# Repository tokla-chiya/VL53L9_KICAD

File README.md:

# VL53L9CX I2C-only breakout

Open `VL53L9.kicad_pro` in KiCad, then open `VL53L9.kicad_sch`.
The schematic is complete; the PCB is still empty and needs placement/routing.

## Interface

Supply regulated 3.3 V through J1. The design assumes a 3.3 V host and uses
U5 to translate SDA, SCL, XSHUT, and INTR to the sensor's 1.8 V domain.
Provide at least 1 A source capacity as a starting design allowance, then
verify rail droop and transient current with the intended ranging profile.

| J1 pin | Signal | Use |
|---|---|---|
| 1 | 3V3 | Power input |
| 2 | GND | Common ground |
| 3 | HOST_SCL | Host I2C clock |
| 4 | HOST_SDA | Host I2C data |
| 5 | HOST_XSHUT | Active-low shutdown/reset control |
| 6 | HOST_INTR | Interrupt to host |

Keep XSHUT low while power starts, then release it after supplies and the
onboard clock stabilize. Configure firmware for a 12 MHz application clock,
2.8 V AVDD, 1.8 V IOVDD, and I2C data readout. The default 7-bit address is
0x29. I2C readout limits frame rate; select resolution and rate accordingly.
SYNC_IN is pulled high for autonomous or software-triggered operation.

## Implementation

- U1 uses the supplied 42-pad sensor footprint, copied unchanged to the local library.
- U2/U3/U4 provide 2.8 V, 1.8 V, and 1.2 V using the reference LDK130 regulators.
- Y1 is the reference ECS-2520MVLC-120-CN-TR oscillator, powered at 1.8 V.
- U5 is PI4ULS3V204LEX (TSSOP-14). This deliberately substitutes the larger
  package for the reference board's TQFN version; order the LEX variant.
- R2/R3 are fitted host pull-ups. R5/R6 are optional sensor-side pull-ups,
  **DNP**, matching the reference population. U5 has internal pull-ups.
- MIPI and reserved pins have explicit no-connect markers. No MIPI connector,
  EEPROM, external clock input, or host voltage-select jumper is included.
- The sensor symbol's pin positions/numbers come from the supplied library;
  electrical types were added so ERC can check inputs and supply connections.

The older reference schematic labels some thermal pads C4-C9 and E3/E5/E12
as VHV/VPP/ATEST0. The supplied library and current datasheet use D4-D9
for those thermal pads, E5 as ground, and E3/E12 as reserved no-connect pins.
This design follows the current pinout.

Place sensor decoupling capacitors immediately beside the associated supply
pads (see each capacitor's Function field). Connect all ground and thermal
pads to a ground plane with thermal vias. Verify package land dimensions,
orientation, thermal performance, and effective capacitor values during PCB
layout. The supplied footprint was checked for matching pad numbers; its
manufacturing geometry has not been independently qualified.

## Review files

- `output/VL53L9-I2C-schematic.pdf`: plotted schematic.
- `output/BOM.md`: 32 components, including two DNP resistors.
- `output/VL53L9.net.xml`: KiCad-exported netlist.
- `output/ERC.json`: zero reported errors or warnings in KiCad 10.0.6.
- `output/verification.json`: independent connectivity and pad checks.
- `backups/VL53L9.blank.kicad_sch`: original empty schematic.

`tools/build_schematic.py` generated the starting schematic. It overwrites
the schematic and local libraries, so do not rerun it after manual edits
unless those edits have been incorporated into the script. Re-export the
netlist/ERC before running `tools/verify_netlist.py` on subsequent changes.

## References

- Supplied `steval-vl53l9-schematic.pdf`, Rev 1, March 2026.
- Supplied `steval-vl53l9-bom.pdf`, Rev 2, May 2026.
- [ST VL53L9CX datasheet, DS14879 Rev 8](https://www.st.com/resource/en/datasheet/vl53l9cx.pdf), pinout and I2C application circuit.
- [Diodes PI4ULS3V204 datasheet](https://www.diodes.com/datasheet/download/PI4ULS3V204.pdf), translator pinout and package.
- [ECS-2520MVLC](https://ecsxtal.com/products/oscillators/surface-mount-oscillators/ecs-2520mvlc/), oscillator family.

These are schematic-level checks, not a hardware validation or a completed PCB design.

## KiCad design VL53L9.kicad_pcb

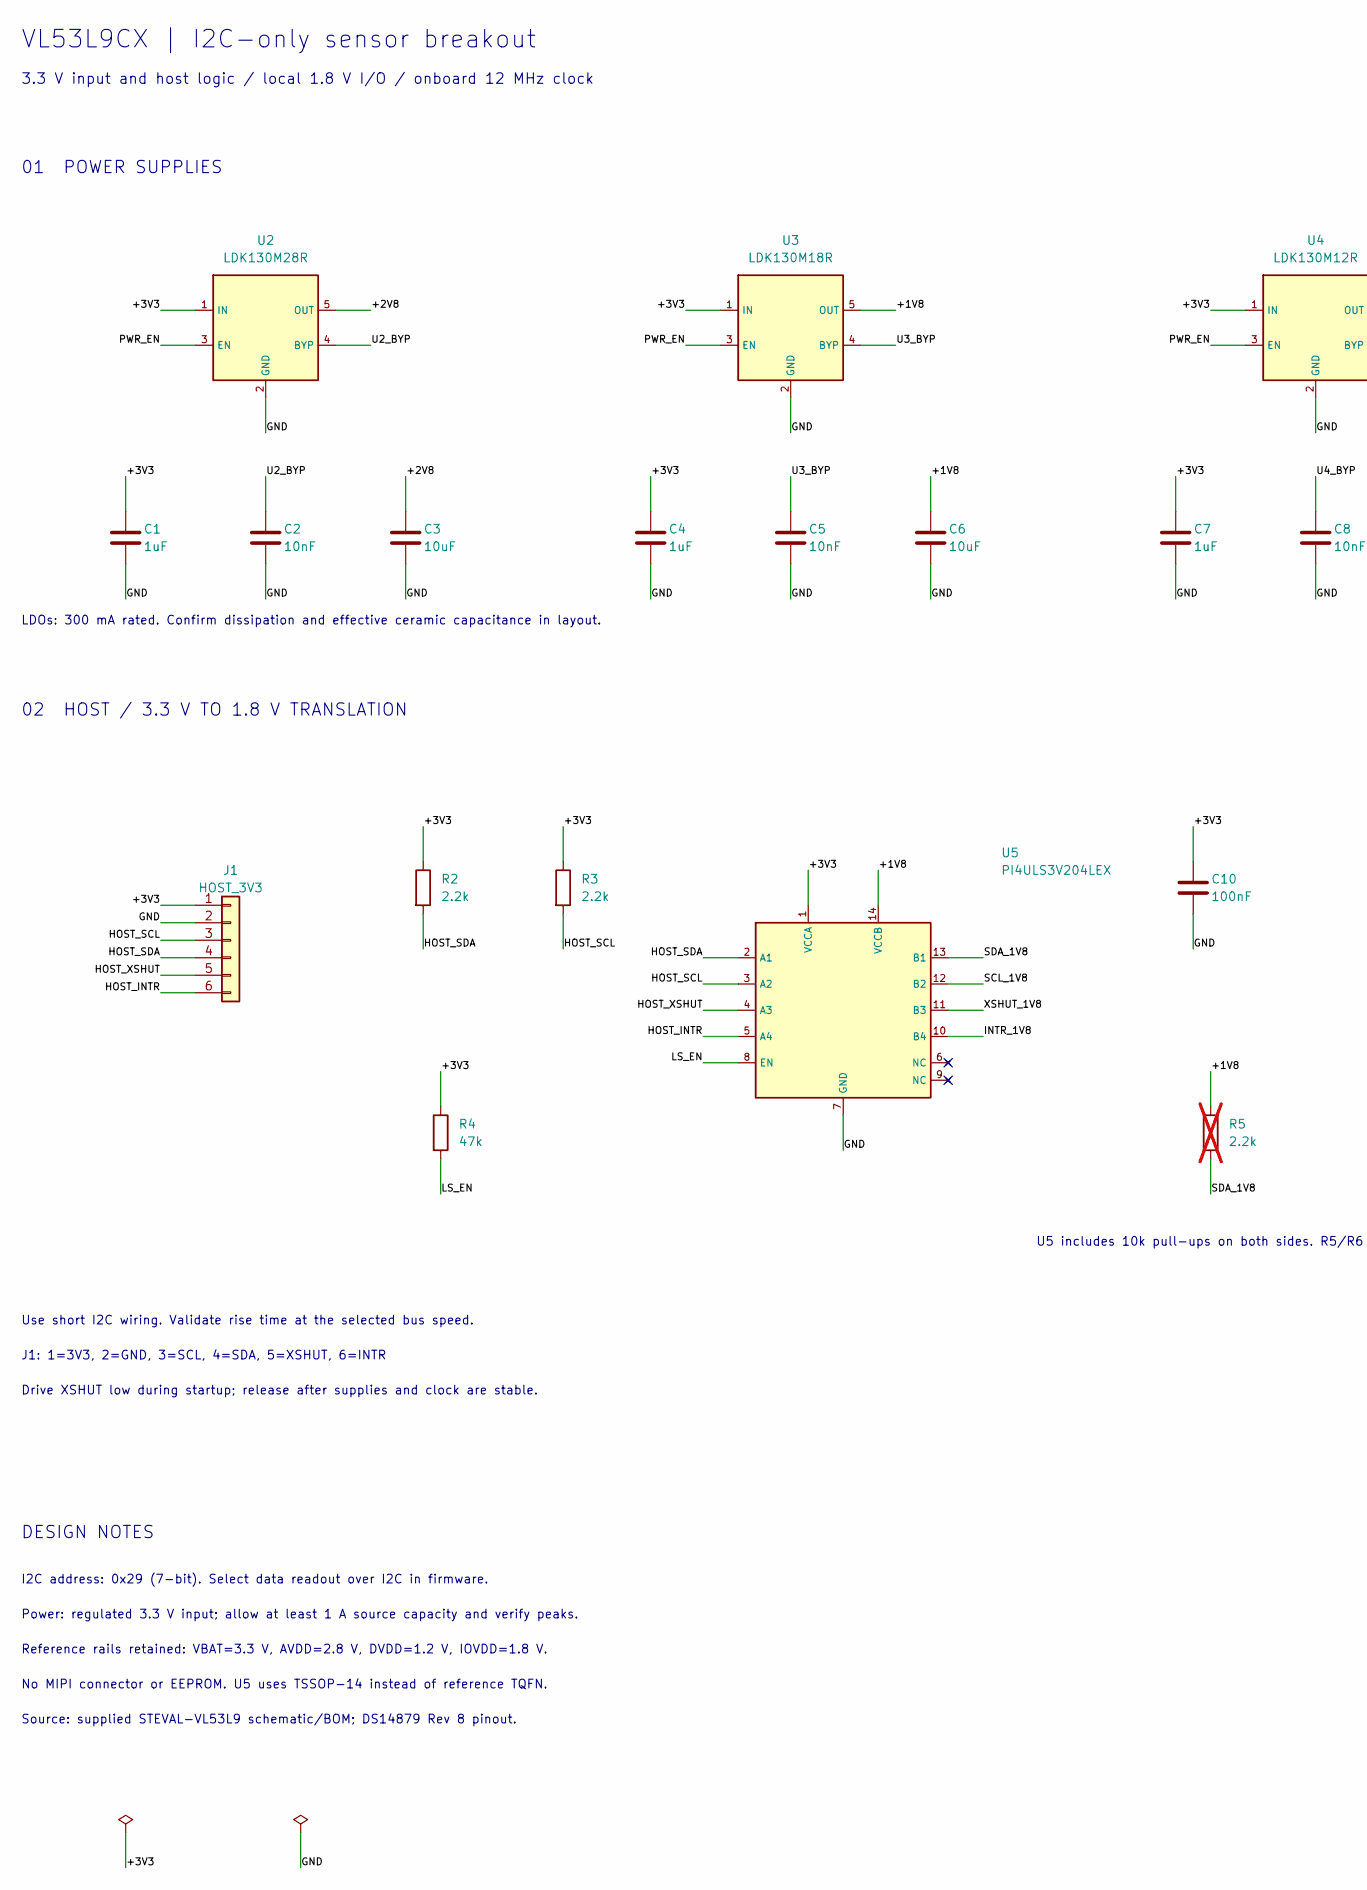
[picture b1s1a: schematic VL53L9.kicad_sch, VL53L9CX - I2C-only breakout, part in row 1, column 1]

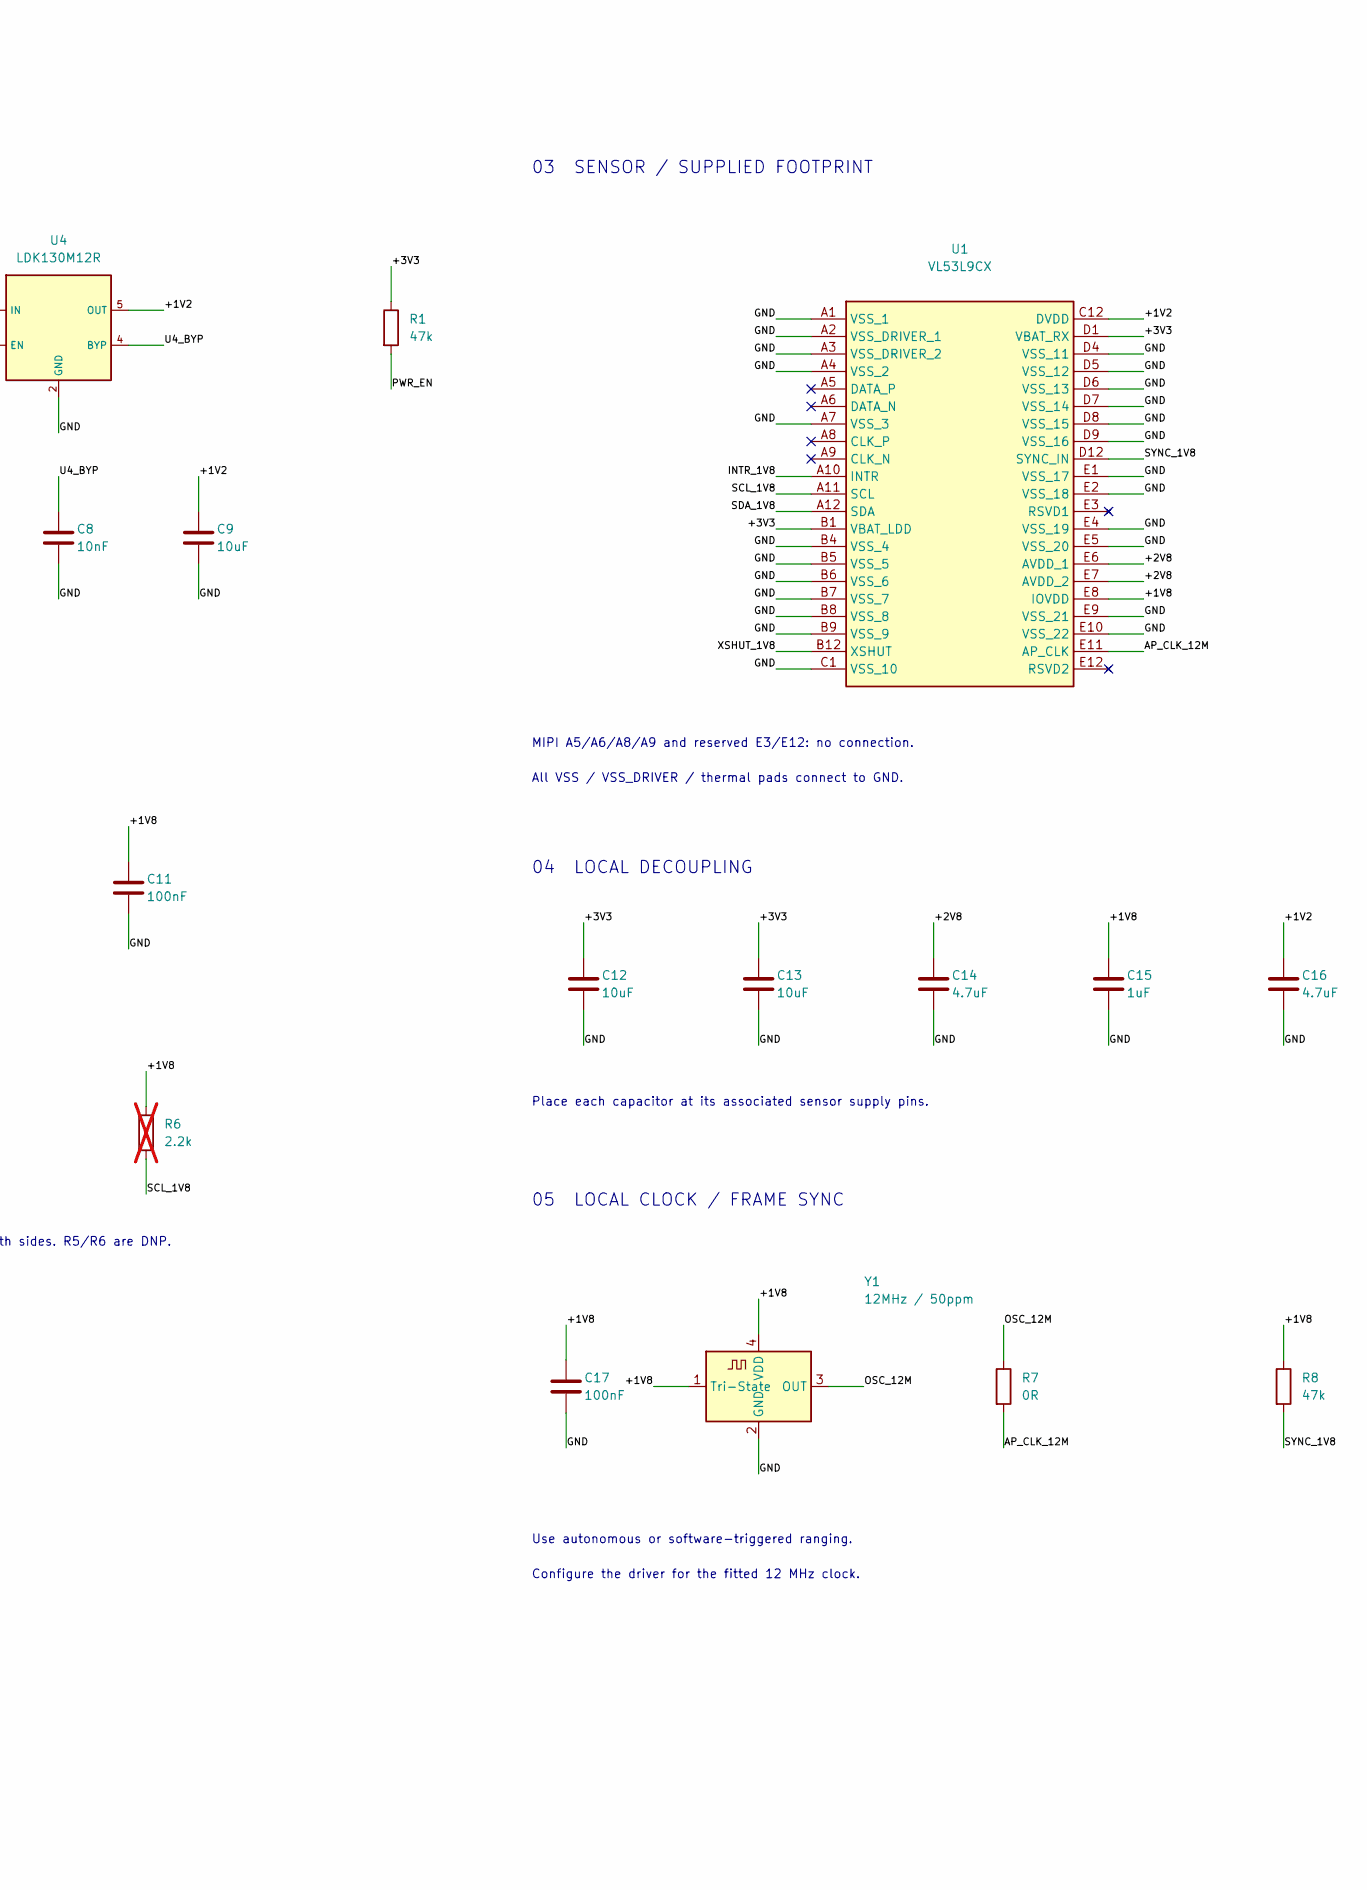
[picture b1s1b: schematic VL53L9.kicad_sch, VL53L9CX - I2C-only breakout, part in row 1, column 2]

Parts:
C1, C4, C7, C15: 1uF; C_0402_1005Metric; MPN GRM155R6YA105KE11D
C2, C5, C8: 10nF; C_0402_1005Metric; MPN 04023D103KAT2A
C3, C6, C9, C12, C13: 10uF; C_0402_1005Metric; MPN GRJ155R60J106ME11D
C10, C11, C17: 100nF; C_0402_1005Metric; MPN GRT155R71H104KE01D
C14, C16: 4.7uF; C_0402_1005Metric; MPN C1005X5R0J475K050BC
J1: HOST_3V3; PinHeader_1x06_P2.54mm_Vertical
R1, R4, R8: 47k; R_0402_1005Metric; MPN ERJ2RKF4702X
R2, R3: 2.2k; R_0402_1005Metric; MPN RC0402FR-072K2L
R5, R6: 2.2k; R_0402_1005Metric; MPN RC0402FR-072K2L; not fitted
R7: 0R; R_0402_1005Metric; MPN RC0402JR-070RL
U1: VL53L9CX; MPN VL53L9CXV0VE/1
U2: LDK130M28R; SOT-23-5; MPN LDK130M28R
U3: LDK130M18R; SOT-23-5; MPN LDK130M18R
U4: LDK130M12R; SOT-23-5; MPN LDK130M12R
U5: PI4ULS3V204LEX; TSSOP-14_4.4x5mm_P0.65mm; MPN PI4ULS3V204LEX
Y1: 12MHz / 50ppm; Oscillator_SMD_ECS_2520MV-xxx-xx-4Pin_2.5x2.0mm; MPN ECS-2520MVLC-120-CN-TR

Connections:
/+1V2: C9.1, C16.1, U1.C12 (DVDD), U4.5 (OUT)
/+1V8: C6.1, C11.1, C15.1, C17.1, R5.1, R6.1, R8.1, U1.E8 (IOVDD), U3.5 (OUT), U5.14 (VCCB), Y1.1 (Tri-State), Y1.4 (VDD)
/+2V8: C3.1, C14.1, U1.E6 (AVDD_1), U1.E7 (AVDD_2), U2.5 (OUT)
/+3V3: C1.1, C4.1, C7.1, C10.1, C12.1, C13.1, J1.1, R1.1, R2.1, R3.1, R4.1, U1.B1 (VBAT_LDD), U1.D1 (VBAT_RX), U2.1 (IN), U3.1 (IN), U4.1 (IN), U5.1 (VCCA)
/AP_CLK_12M: R7.2, U1.E11 (AP_CLK)
/GND: C1.2, C2.2, C3.2, C4.2, C5.2, C6.2, C7.2, C8.2, C9.2, C10.2, C11.2, C12.2, C13.2, C14.2, C15.2, C16.2, C17.2, J1.2, U1.A1 (VSS_1), U1.A2 (VSS_DRIVER_1), U1.A3 (VSS_DRIVER_2), U1.A4 (VSS_2), U1.A7 (VSS_3), U1.B4 (VSS_4), U1.B5 (VSS_5), U1.B6 (VSS_6), U1.B7 (VSS_7), U1.B8 (VSS_8), U1.B9 (VSS_9), U1.C1 (VSS_10), U1.D4 (VSS_11), U1.D5 (VSS_12), U1.D6 (VSS_13), U1.D7 (VSS_14), U1.D8 (VSS_15), U1.D9 (VSS_16), U1.E1 (VSS_17), U1.E2 (VSS_18), U1.E4 (VSS_19), U1.E5 (VSS_20), U1.E9 (VSS_21), U1.E10 (VSS_22), U2.2 (GND), U3.2 (GND), U4.2 (GND), U5.7 (GND), Y1.2 (GND)
/HOST_INTR: J1.6, U5.5 (A4)
/HOST_SCL: J1.3, R3.2, U5.3 (A2)
/HOST_SDA: J1.4, R2.2, U5.2 (A1)
/HOST_XSHUT: J1.5, U5.4 (A3)
/INTR_1V8: U1.A10 (INTR), U5.10 (B4)
/LS_EN: R4.2, U5.8 (EN)
/OSC_12M: R7.1, Y1.3 (OUT)
/PWR_EN: R1.2, U2.3 (EN), U3.3 (EN), U4.3 (EN)
/SCL_1V8: R6.2, U1.A11 (SCL), U5.12 (B2)
/SDA_1V8: R5.2, U1.A12 (SDA), U5.13 (B1)
/SYNC_1V8: R8.2, U1.D12 (SYNC_IN)
/U2_BYP: C2.1, U2.4 (BYP)
/U3_BYP: C5.1, U3.4 (BYP)
/U4_BYP: C8.1, U4.4 (BYP)
/XSHUT_1V8: U1.B12 (XSHUT), U5.11 (B3)

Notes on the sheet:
VL53L9CX | I2C-only sensor breakout
3.3 V input and host logic / local 1.8 V I/O / onboard 12 MHz clock
01 POWER SUPPLIES
LDOs: 300 mA rated. Confirm dissipation and effective ceramic capacitance in layout.
02 HOST / 3.3 V TO 1.8 V TRANSLATION
U5 includes 10k pull-ups on both sides. R5/R6 are DNP.
Use short I2C wiring. Validate rise time at the selected bus speed.
J1: 1=3V3, 2=GND, 3=SCL, 4=SDA, 5=XSHUT, 6=INTR
Drive XSHUT low during startup; release after supplies and clock are stable.
03 SENSOR / SUPPLIED FOOTPRINT
MIPI A5/A6/A8/A9 and reserved E3/E12: no connection.
All VSS / VSS_DRIVER / thermal pads connect to GND.
04 LOCAL DECOUPLING
Place each capacitor at its associated sensor supply pins.
05 LOCAL CLOCK / FRAME SYNC
Use autonomous or software-triggered ranging.
Configure the driver for the fitted 12 MHz clock.
DESIGN NOTES
I2C address: 0x29 (7-bit). Select data readout over I2C in firmware.
Power: regulated 3.3 V input; allow at least 1 A source capacity and verify peaks.
Reference rails retained: VBAT=3.3 V, AVDD=2.8 V, DVDD=1.2 V, IOVDD=1.8 V.
No MIPI connector or EEPROM. U5 uses TSSOP-14 instead of reference TQFN.
Source: supplied STEVAL-VL53L9 schematic/BOM; DS14879 Rev 8 pinout.

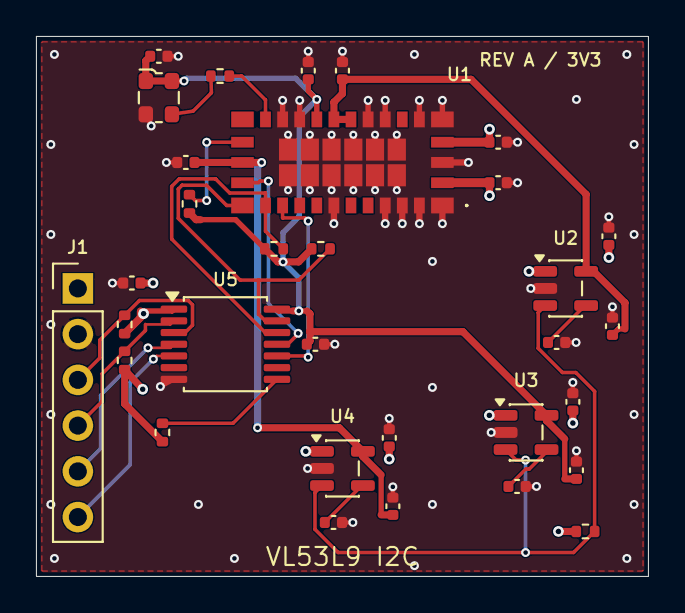
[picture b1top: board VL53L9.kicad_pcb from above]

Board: 4 copper layers, 34.0 x 30.0 mm, 32 parts (0 on the bottom side), 21 nets.

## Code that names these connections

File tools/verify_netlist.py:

"""Independent checks of KiCad's exported connectivity and assigned footprints."""
from pathlib import Path
import xml.etree.ElementTree as ET
import re, json

root=Path(__file__).resolve().parents[1]
doc=ET.parse(root/'output/VL53L9.net.xml').getroot()
nets={n.attrib['name'].lstrip('/'): {(p.attrib['ref'],p.attrib['pin']) for p in n.findall('node')} for n in doc.findall('nets/net')}
pins={pin:net for net,members in nets.items() for pin in members}
expected={
 'B1':'+3V3','D1':'+3V3','E6':'+2V8','E7':'+2V8','C12':'+1V2','E8':'+1V8',
 'A11':'SCL_1V8','A12':'SDA_1V8','A10':'INTR_1V8','B12':'XSHUT_1V8','D12':'SYNC_1V8','E11':'AP_CLK_12M',
}
grounds='A1 A2 A3 A4 A7 B4 B5 B6 B7 B8 B9 C1 D4 D5 D6 D7 D8 D9 E1 E2 E4 E5 E9 E10'.split()
expected.update({p:'GND' for p in grounds})
for p,net in expected.items(): assert pins[('U1',p)]==net,(p,net,pins.get(('U1',p)))
for p in 'A5 A6 A8 A9 E3 E12'.split():
    net=pins[('U1',p)]
    assert net.startswith('unconnected-') and nets[net]=={('U1',p)}
for p,net in enumerate(['+3V3','GND','HOST_SCL','HOST_SDA','HOST_XSHUT','HOST_INTR'],1): assert pins[('J1',str(p))]==net
for p,net in {'1':'+3V3','14':'+1V8','7':'GND','2':'HOST_SDA','3':'HOST_SCL','4':'HOST_XSHUT','5':'HOST_INTR','13':'SDA_1V8','12':'SCL_1V8','11':'XSHUT_1V8','10':'INTR_1V8'}.items(): assert pins[('U5',p)]==net
for u,rail in [('U2','+2V8'),('U3','+1V8'),('U4','+1V2')]:
    for p,net in {'1':'+3V3','2':'GND','3':'PWR_EN','4':u+'_BYP','5':rail}.items(): assert pins[(u,p)]==net
for p,net in {'1':'+1V8','2':'GND','3':'OSC_12M','4':'+1V8'}.items(): assert pins[('Y1',p)]==net
assert nets['OSC_12M']=={('Y1','3'),('R7','1')}
assert nets['AP_CLK_12M']=={('R7','2'),('U1','E11')}
for c,net in [('C12','+3V3'),('C13','+3V3'),('C14','+2V8'),('C15','+1V8'),('C16','+1V2')]:
    assert pins[(c,'1')]==net and pins[(c,'2')]=='GND'
fpbase=Path('C:/Program Files/KiCad/10.0/share/kicad/footprints')
footprints={}
for c in doc.findall('components/comp'):
    lib,name=c.findtext('footprint').split(':')
    path=(root/'libraries/VL53L9_Local.pretty' if lib=='VL53L9_Local' else fpbase/(lib+'.pretty'))/(name+'.kicad_mod')
    assert path.exists(),path
    padnums=set(re.findall(r'\(pad\s+"?([^"\s()]+)"?\s',path.read_text()))
    used={p for (ref,p) in pins if ref==c.attrib['ref']}
    assert used<=padnums,(c.attrib['ref'],used-padnums)
    footprints[c.attrib['ref']]=str(path)
assert len([p for p in pins if p[0]=='U1'])==42
supplied=root/'LIB_VL53L9CX/VL53L9CX/KiCad/VL53L9CX.kicad_mod'
assert supplied.read_bytes()==Path(footprints['U1']).read_bytes()
erc=json.loads((root/'output/ERC.json').read_text())
assert not any(s['violations'] for s in erc['sheets'])
result={'status':'passed','components':len(footprints),'sensor_pins_checked':42,'ground_pads_checked':len(grounds),'erc_errors_and_warnings':0,'checks':['Sensor pinout vs DS14879 Rev 8','J1 pinout and voltage domains','Translator mapping','Regulator pinouts and rails','Clock path','Five local sensor decoupling capacitors','MIPI and reserved pins isolated','All component footprints exist and contain connected pads','Supplied sensor footprint preserved byte-for-byte']}
(root/'output/verification.json').write_text(json.dumps(result,indent=2))
print(json.dumps(result,indent=2))
